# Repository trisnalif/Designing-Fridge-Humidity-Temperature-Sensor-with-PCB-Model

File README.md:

# Designing-Fridge-Humidity-Temperature-Sensor-with-PCB-Model

A custom wireless environmental monitoring system designed to track refrigerator temperature and humidity in real time. Built around the **ATmega328P** microcontroller, this project consists of a battery-powered **Transmitter** unit placed inside the fridge and a **Receiver** display unit positioned outside.

---

## System Architecture

### 1. Transmitter Unit (`Fridge_Transmitter`)
The transmitter unit collects ambient temperature and relative humidity data inside the refrigerator and broadcasts it wirelessly via an RF transmitter module.
* **Microcontroller:** ATmega328P (with external crystal oscillator & 22pF load capacitors)
* **Sensor:** AM2302 (DHT22) Digital Temperature & Humidity Sensor with 10kΩ pull-up resistor
* **Wireless Module:** 4-pin RF Transmitter module with external antenna (`AE1`)
* **Power Supply:** 9V battery input with dual Zener-regulated rails (**5V** via `D1` and **3.3V** via `D2`) and 100µF decoupling capacitors
* **Controls:** Tactile reset push-button (`SW2`) with 10kΩ pull-up and 100nF debounce capacitor

### 2. Receiver Unit (`Fridge_Receiver`)
The receiver unit captures incoming RF packets from the transmitter, processes the telemetry data, and displays the readings locally.
* **Microcontroller:** ATmega328P clocked by a 16MHz crystal oscillator (`Y1`)
* **Wireless Module:** RF Receiver module (`J1`) with external antenna (`AE1`)
* **Display:** 16x2 Character LCD (`LCD-016N002L`) operating in 4-bit mode (`DB4–DB7`) with a 10kΩ contrast adjustment potentiometer (`RV1`)
* **Power Supply:** 9V battery regulated down to a stable **5V** rail using an **L7805** linear voltage regulator (`U3`) with 470µF, 10µF, and 100nF filtering capacitors
* **Controls:** Tactile reset push-button (`SW1`)

---

## Tools & Workflow
* **EDA Software:** KiCad (Schematic Capture & KiCad PCB Layout)
* **Hardware Design:** Through-Hole (THT) & SMD mixed prototyping, DRC/ERC verified

* ## Documentary
* 
Image 1. Transmitter Schematic

Image 2. Transmitter PCB Model

Image 3. Top Look

Image 4. Bottom Look

Image 5. Receiver Schematic

Image 6. Receiver PCB

Image 7. Top Look

Image 8. Bottom Look

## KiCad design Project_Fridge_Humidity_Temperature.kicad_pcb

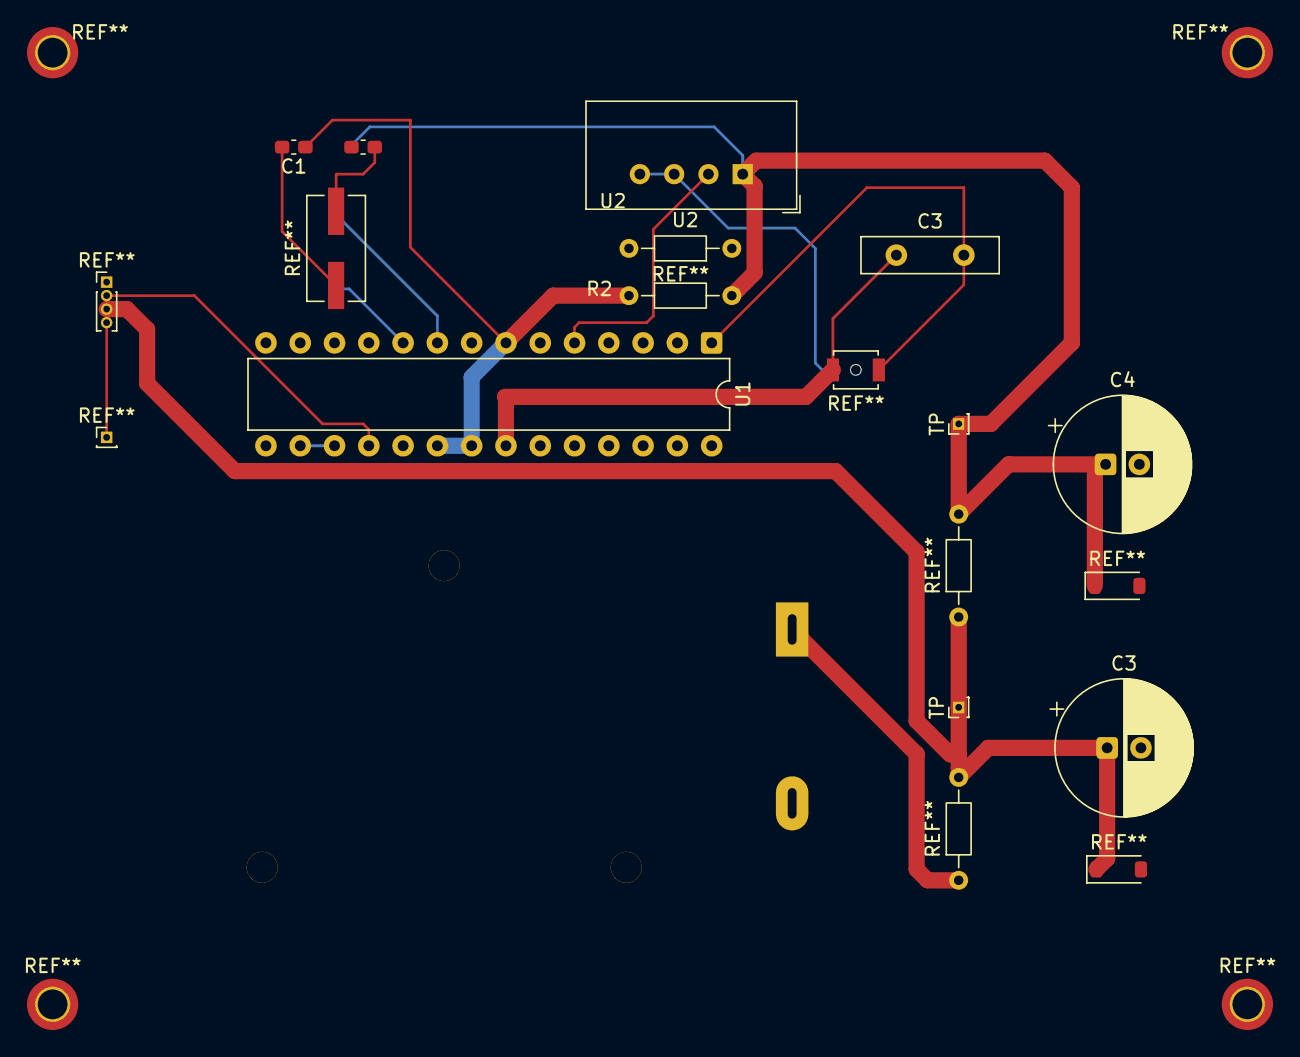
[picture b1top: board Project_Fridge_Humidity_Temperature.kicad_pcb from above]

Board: 2 copper layers, 10 parts (0 on the bottom side), 7 nets.

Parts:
C1, C2: 100u; C_0603_1608Metric_Pad1.08x0.95mm_HandSolder
C3: 100n; CP_Radial_D10.0mm_P2.50mm
C3#2: 100n; C_Disc_D10.0mm_W2.5mm_P5.00mm
C4: 22p; CP_Radial_D10.0mm_P2.50mm
R2: 100; R_Axial_DIN0204_L3.6mm_D1.6mm_P7.62mm_Horizontal
TP: TP1; PinHeader_1x01_P1.00mm_Vertical
TP#2: TP1; PinHeader_1x01_P1.00mm_Vertical
U1: ATmega328-P; DIP-28_W7.62mm
U2: AM2302; ASAIR_AM2302_P2.54mm_Vertical

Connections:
GNDREF: C3.1, C4.1, U1.8 (GND), U1.22 (GND), U2.3 (GND), U2.4 (GND)
unnamed: C1.2, C2.2
unnamed: C1.1, R2.1, U1.7 (VCC), U1.20 (AVCC), U1.21 (AREF)
unnamed: C2.1, R2.2, U2.1 (VDD)
unnamed: C3.2, U1.1 (~RESET/PC6)
unnamed: U1.5 (PD3), U2.2 (SDA)
unnamed: C4.2, U1.10 (XTAL2/PB7)

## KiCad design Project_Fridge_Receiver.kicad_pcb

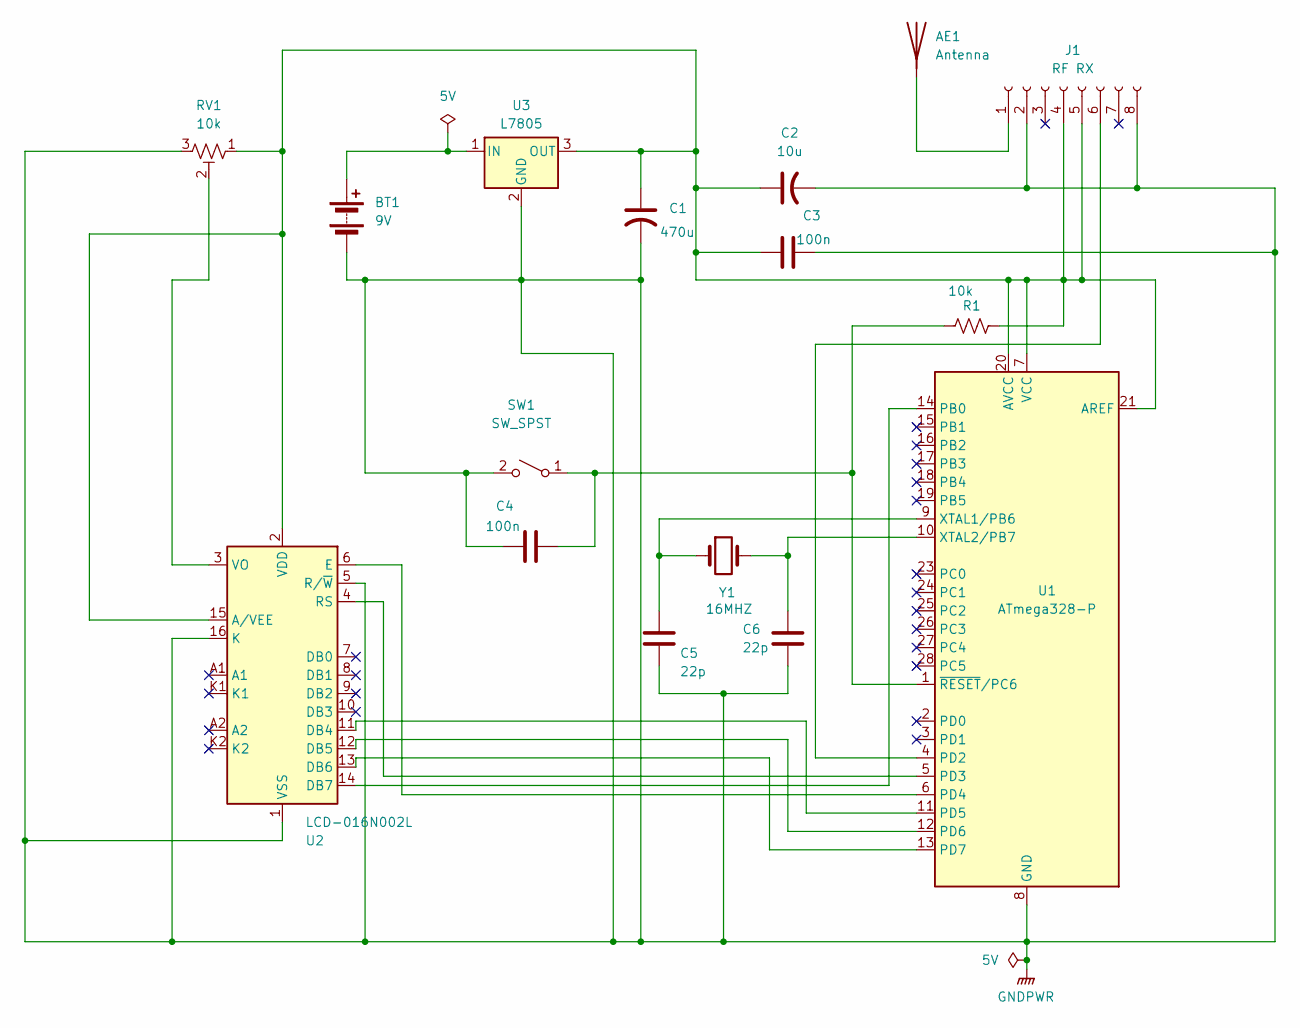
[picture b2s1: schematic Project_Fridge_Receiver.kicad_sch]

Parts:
AE1: Antenna; PinHeader_1x01_P1.00mm_Horizontal
BT1: 9V; BatteryHolder_MPD_BA9VPC_1xPP3
C1: 470u; CP_Radial_D10.0mm_P5.00mm
C2: 10u; CP_Radial_D5.0mm_P2.50mm
C3, C4: 100n; R_Axial_DIN0207_L6.3mm_D2.5mm_P10.16mm_Horizontal
C5, C6: 22p; C_Disc_D11.0mm_W5.0mm_P7.50mm
J1: RF RX; PinHeader_1x08_P1.00mm_Vertical
R1: 10k; R_Axial_DIN0207_L6.3mm_D2.5mm_P10.16mm_Horizontal
RV1: 10k; Potentiometer_Bourns_3296W_Vertical
SW1: SW_SPST; SW_SPST_B3U-1000P-B
U1: ATmega328-P; DIP-28_W7.62mm
U2: LCD-016N002L
U3: L7805; TO255P1040X460X1968-3
Y1: 16MHZ; Crystal_HC49-U_Vertical

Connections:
GNDPWR: BT1.2 (-), C1.2, C2.2, C3.2, C4.1, C5.2, C6.2, J1.2, J1.8, RV1.3, SW1.2 (B), U1.8 (GND), U1.22 (GND), U2.1 (VSS), U2.5 (R/~W), U2.16 (K), U3.2 (GND)
unnamed: AE1.1 (A_1), J1.1
unnamed: BT1.1 (+), U3.1 (IN)
unnamed: C1.1, C2.1, C3.1, J1.4, J1.5, R1.2, RV1.1, U1.7 (VCC), U1.20 (AVCC), U1.21 (AREF), U2.2 (VDD), U2.15 (A/VEE), U3.3 (OUT)
unnamed: J1.6, U1.4 (PD2)
unnamed: C4.2, R1.1, SW1.1 (A), U1.1 (~RESET/PC6)
unnamed: U1.14 (PB0), U2.14 (DB7)
unnamed: U1.5 (PD3), U2.4 (RS)
unnamed: U1.6 (PD4), U2.6 (E)
unnamed: U1.11 (PD5), U2.11 (DB4)
unnamed: U1.12 (PD6), U2.12 (DB5)
unnamed: U1.13 (PD7), U2.13 (DB6)
unnamed: C5.1, U1.9 (XTAL1/PB6), Y1.1
unnamed: C6.1, U1.10 (XTAL2/PB7), Y1.2
unnamed: RV1.2, U2.3 (VO)

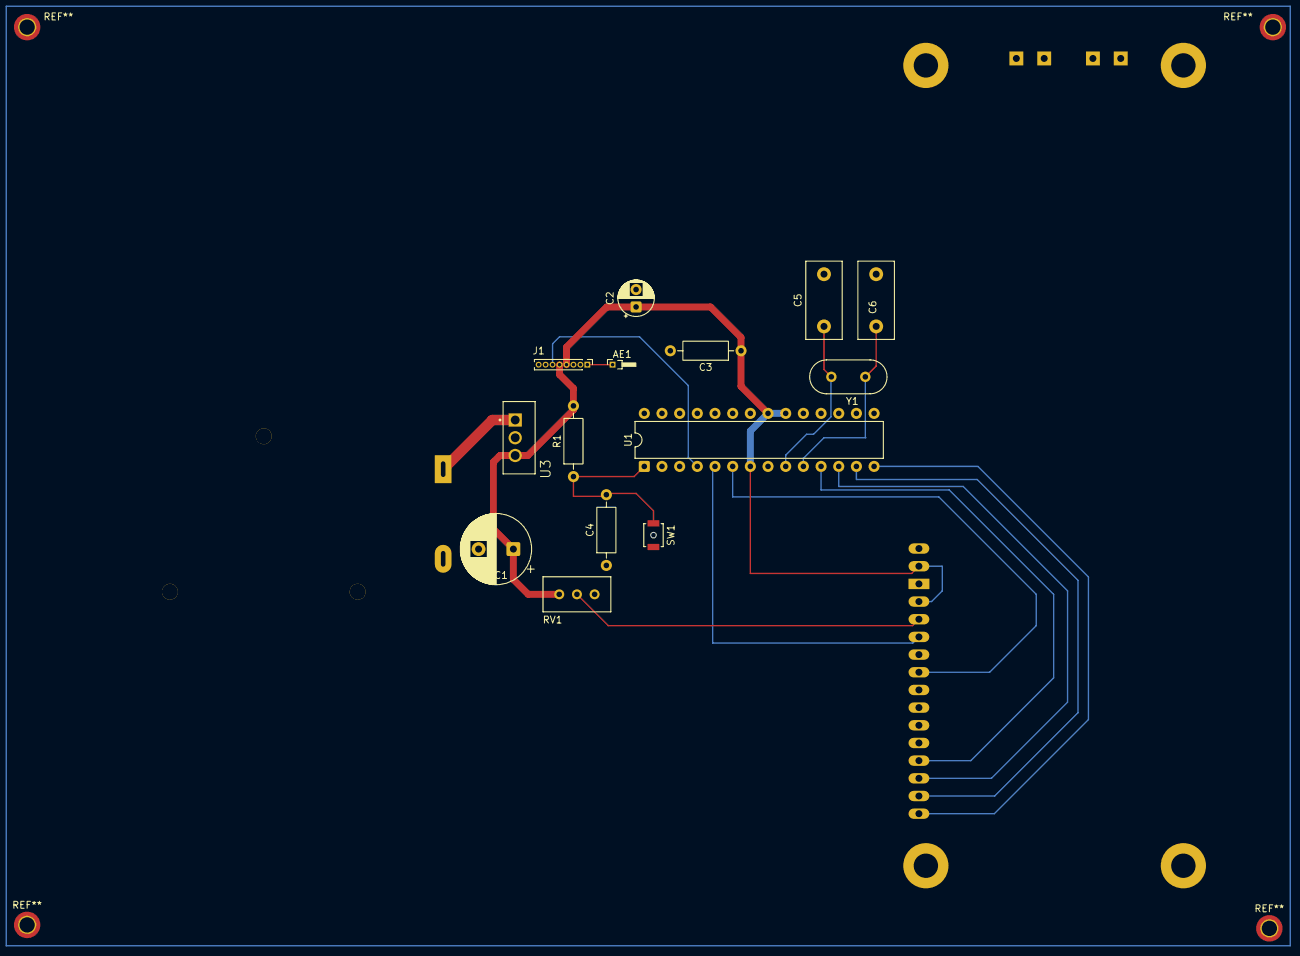
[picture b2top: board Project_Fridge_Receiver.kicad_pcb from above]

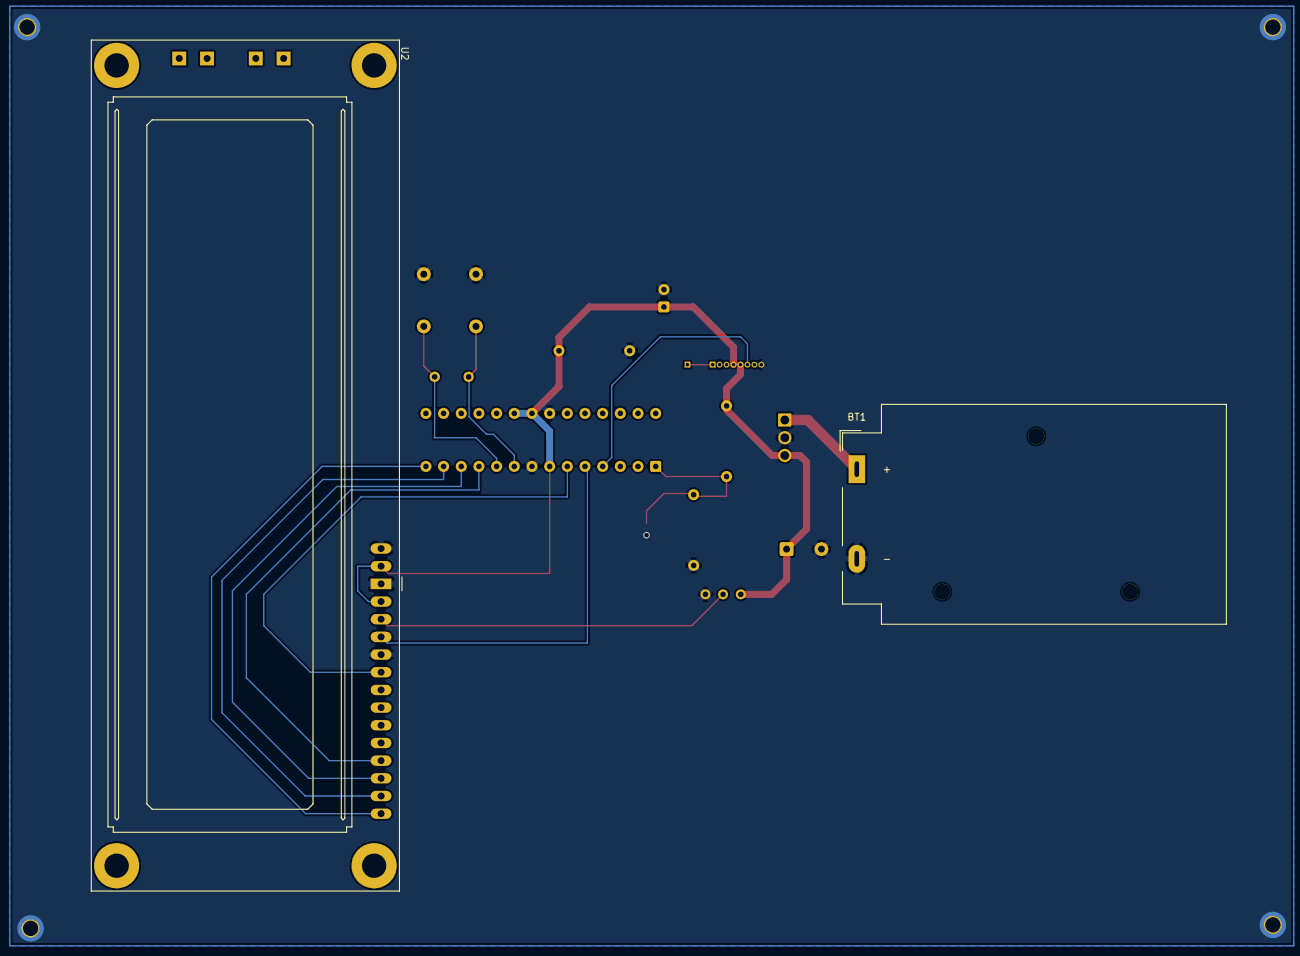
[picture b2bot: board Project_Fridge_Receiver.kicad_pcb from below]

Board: 2 copper layers, 16 parts (2 on the bottom side), 15 nets.
